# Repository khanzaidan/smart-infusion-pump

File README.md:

# 🏥 Smart Infusion Pump
### STM32F407 + FreeRTOS | Medical Grade | IEC 62304 Aligned

> Developed during Embedded R&D Internship at **Walnut Medical, Mohali**

---

## 📋 Project Overview
A safety-critical smart infusion pump featuring closed-loop PID flow 
control, real-time RTOS scheduling, Peltier temperature regulation, 
and WiFi monitoring — built on STM32F407VGT6 with FreeRTOS.

---

## 🔧 Hardware Architecture

| Component | Part | Function |
|-----------|------|----------|
| Main MCU | STM32F407VGT6 | FreeRTOS controller |
| Safety MCU | ATmega328P | Independent watchdog |
| WiFi | ESP32-WROOM-32UE | Remote monitoring |
| Motor Driver | DRV8825 | NEMA17 stepper |
| Pressure | MPRLS0015PG | Flow sensing |
| Temperature | DS18B20 x2 | Peltier control |
| Bubble Detect | BSTH-003 | Safety detection |
| Battery | BQ24650 + MAX17043 | Power management |
| Display | SSD1306 OLED | User interface |

---

## 🧵 FreeRTOS Task Structure

| Task | Priority | Stack |
|------|----------|-------|
| vMotorControlTask | AboveNormal | 512 |
| vSafetyMonitorTask | Realtime | 256 |
| vTemperatureTask | Normal | 256 |
| vDisplayTask | BelowNormal | 512 |
| vCommunicationTask | BelowNormal | 512 |
| vPressureTask | Normal | 256 |

---

## 📌 STM32F407 Pin Assignments

| Signal | Pin | Function |
|--------|-----|----------|
| USART1_TX/RX | PA9/PA10 | ESP32 WiFi |
| USART3_TX/RX | PD8/PD9 | ATmega Safety |
| I2C1_SCL/SDA | PB6/PB7 | OLED + EEPROM |
| I2C2_SCL/SDA | PB10/PB11 | Pressure + Fuel |
| TIM2_CH1 | PA0 | Peltier PWM |
| STEP_PUL/DIR/EN | PD11/PD12/PD13 | DRV8825 |
| TEMP_OW | PC9 | DS18B20 |
| RELAY_CTRL | PB15 | Motor Relay |
| BUZZ_SIG | PE1 | Buzzer |
| FAN_CTRL | PC8 | Cooling Fan |

---

## ⚙️ Clock Configuration
- HSE Crystal: 8MHz
- PLL: M=8, N=336, P=2
- SYSCLK: **168MHz**
- APB1: 42MHz | APB2: 84MHz

---

## 📐 PCB Specifications
- **Board Size:** 120mm x 100mm
- **Layers:** 2-layer with GND pour
- **Components:** 186
- **DRC Violations:** 0
- **Status:** Gerbers submitted to manufacturer

---

## 🛡️ Safety Features
- ATmega328P independent safety watchdog
- TPS3823 hardware watchdog timer
- Overcurrent protection
- Bubble detection alarm
- Limit switch monitoring
- Fault detection FSM
- EEPROM non-volatile parameter storage

---

[Browse the firmware by processor](docs/firmware-map.md)

## 📁 Repository Structure

```
smart-infusion-pump/
├── Core/                       STM32 application, headers and startup
├── Drivers/                    CMSIS and STM32 HAL
├── Middlewares/                FreeRTOS and middleware
├── SMART_INFUSION.ioc          STM32CubeMX configuration
├── SMART_INFUSION_ATmega/      ATmega companion sketch
├── SMART_INFUSION_ESP32/       ESP32 companion sketch
└── docs/firmware-map.md        Source index by processor
```

---

## 👤 Author
**Zaidan Khan** — Embedded R&D Intern @ Walnut Medical  
📧 khanzaidaan786@gmail.com  
🔗 [LinkedIn](https://linkedin.com/in/zaidan-khan-ab30922aa)

## Reference hardware files

[Telemetry observation fixture](hardware/README.md) is a newly drawn bench interface for this project. The hardware guide includes the pinout, KiCad and Altium projects, schematic PDF, routed PCB image, BOM, fabrication artwork and validation reports.

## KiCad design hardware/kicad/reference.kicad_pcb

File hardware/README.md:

# Telemetry observation fixture

Revision A · Reference hardware for Smart Infusion Pump

A passive two-channel observation card for replaying STM32 telemetry on the bench. One channel corresponds to USART1_TX (PA9) and the other to USART3_TX (PD8) in the checked-in CubeMX file.

This circuit was drawn for the portfolio from the interface description. Its connector numbering, board outline and part placements belong to this revision. Original product CAD, connector pinouts and measured results were unavailable. Physical bring-up is pending.

The top view overlays front copper in red, back copper in blue and silkscreen in brown. The board measures 63.50 × 45.72 mm. It uses two copper layers, plated through-hole components and 0.30 mm traces.

## Design files

| File | Use |
| --- | --- |
| [KiCad project](kicad/reference.kicad_pro) | Open in KiCad 9 with the included symbol table and symbol library. |
| [Altium project](altium/reference.PrjPcb) | Open the project with the adjacent native [schematic](altium/reference.SchDoc) and [PCB](altium/reference.PcbDoc). Components and land patterns are embedded in the placed documents. |
| [Schematic PDF](images/schematic.pdf) | Zoom or print the circuit, pin numbers and signal labels. |
| [PCB top view](images/copper.svg) | Inspect both routed copper layers and the assembly markings. |
| [Bill of materials](bom.csv) | Select parts to match the footprint and population notes. |
| [Gerber and drill ZIP](gerbers-and-drill.zip) | Review the manufacturing artwork for this reference revision. |

## Interface and wiring

Connect a development board or signal generator only. The card has no path back to an MCU RX pin, motor drive, fluid circuit or patient connection. Both analyzer channels are 3.3 V logic inputs.

Read the pin numbers from the component side. On each header the square pad marks pin 1. Use the table when wiring an external module.

| Header | Connector | Pin | Signal |
| --- | --- | ---: | --- |
| J1 | BENCH SRC | 1 | `GND` |
| J1 | BENCH SRC | 2 | `PA9_TX1` |
| J1 | BENCH SRC | 3 | `PD8_TX3` |
| J2 | ANALYZER | 1 | `GND` |
| J2 | ANALYZER | 2 | `MON_TX1` |
| J2 | ANALYZER | 3 | `MON_TX3` |

## Assembly and bench checks

Fit the headers and components according to the BOM. Confirm LED polarity where fitted. Check the board for shorts before attaching external equipment.

1. Confirm each source-to-monitor path measures approximately 1 kilohm and both channels are isolated from each other.
2. Replay two independent UART streams from a bench generator. Capture each output separately and confirm that interrupting the analyzer has no effect on the generator.

## Firmware connection

The original STM32 pin configuration identifies PA9 and PD8 as transmit outputs. Use a development board or a synthetic UART source to test capture. [Pinned CubeMX configuration](https://github.com/khanzaidan/smart-infusion-pump/blob/533e038e8589ce8a454668a1a26a9ea66db71109/SMART_INFUSION.ioc)

## Validation

KiCad 9.0.2 reported zero electrical-rule violations, zero PCB design-rule violations, zero unconnected pads and zero schematic-to-board parity errors. The exported schematic netlist matched the specified 10 pin assignments on 5 named nets. [Electrical report](validation/erc.rpt) · [PCB report](validation/drc.rpt)

The Altium files were read back with AltiumSharp. Connectivity reconstructed from the schematic geometry matched the net on each PCB pad. KiCad independently imported the Altium PCB and verified component designators, pad net names, pad widths and drill sizes, trace and via counts, and board dimensions. Altium Designer desktop opening, compilation, manufacturing review and physical measurements are pending.

## Sources

Project background follows the supplied résumé. KiCad Community through-hole land patterns are distributed under CC BY-SA 4.0 with the KiCad design exception. The layout image is a CAD plot of this board. [KiCad library license](https://www.kicad.org/libraries/license/) · [AltiumSharp file writer](https://github.com/issus/AltiumSharp/tree/5caeff2fc0b15c9b63f226ba3f872c65f7f39486)

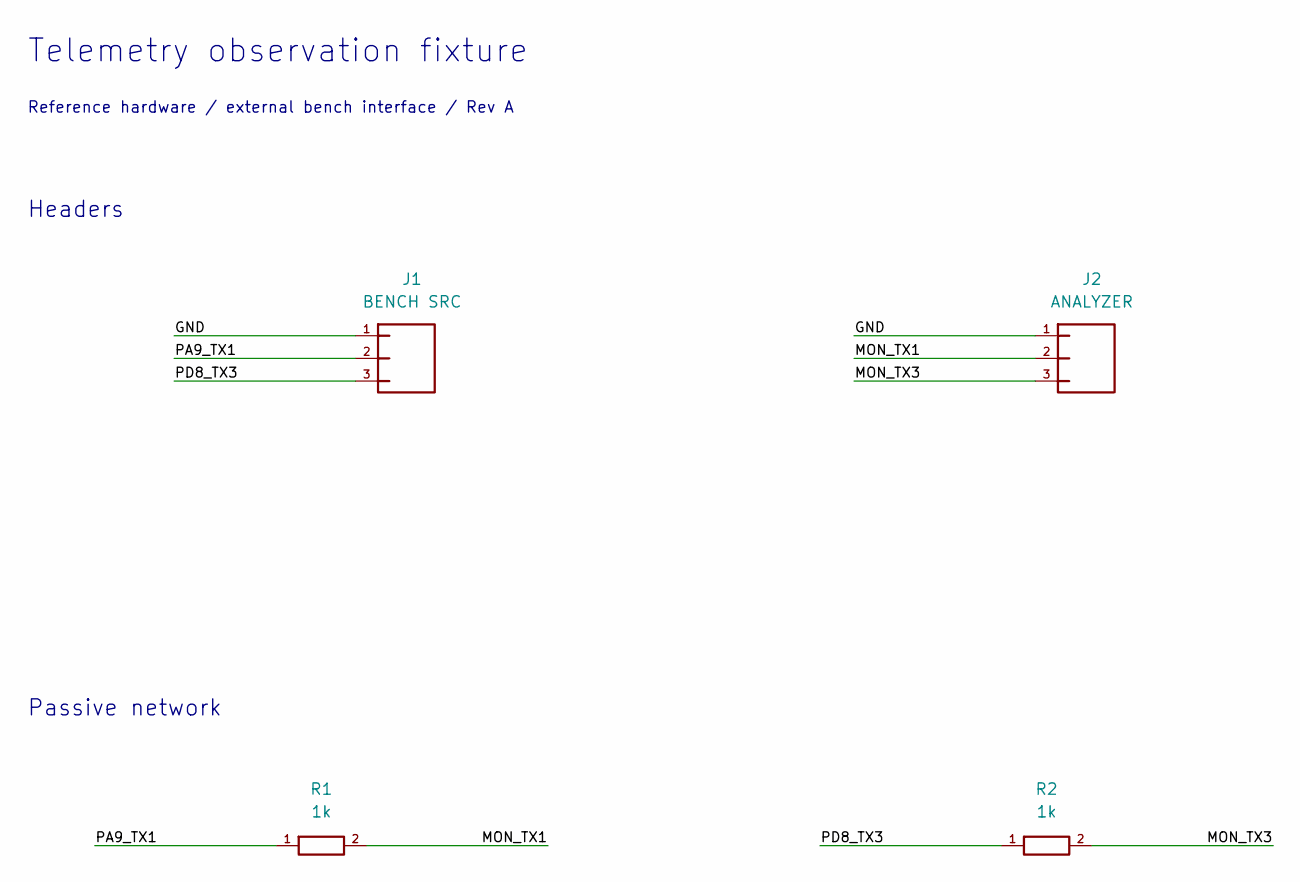
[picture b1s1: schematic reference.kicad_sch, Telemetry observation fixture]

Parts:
J1: BENCH SRC; PinHeader_1x03_P2.54mm_Vertical
J2: ANALYZER; PinHeader_1x03_P2.54mm_Vertical
R1, R2: 1k; R_Axial_DIN0207_L6.3mm_D2.5mm_P7.62mm_Horizontal

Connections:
/GND: J1.1, J2.1
/MON_TX1: J2.2, R1.2
/MON_TX3: J2.3, R2.2
/PA9_TX1: J1.2, R1.1
/PD8_TX3: J1.3, R2.1

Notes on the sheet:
Telemetry observation fixture
Reference hardware / external bench interface / Rev A
Headers
Passive network

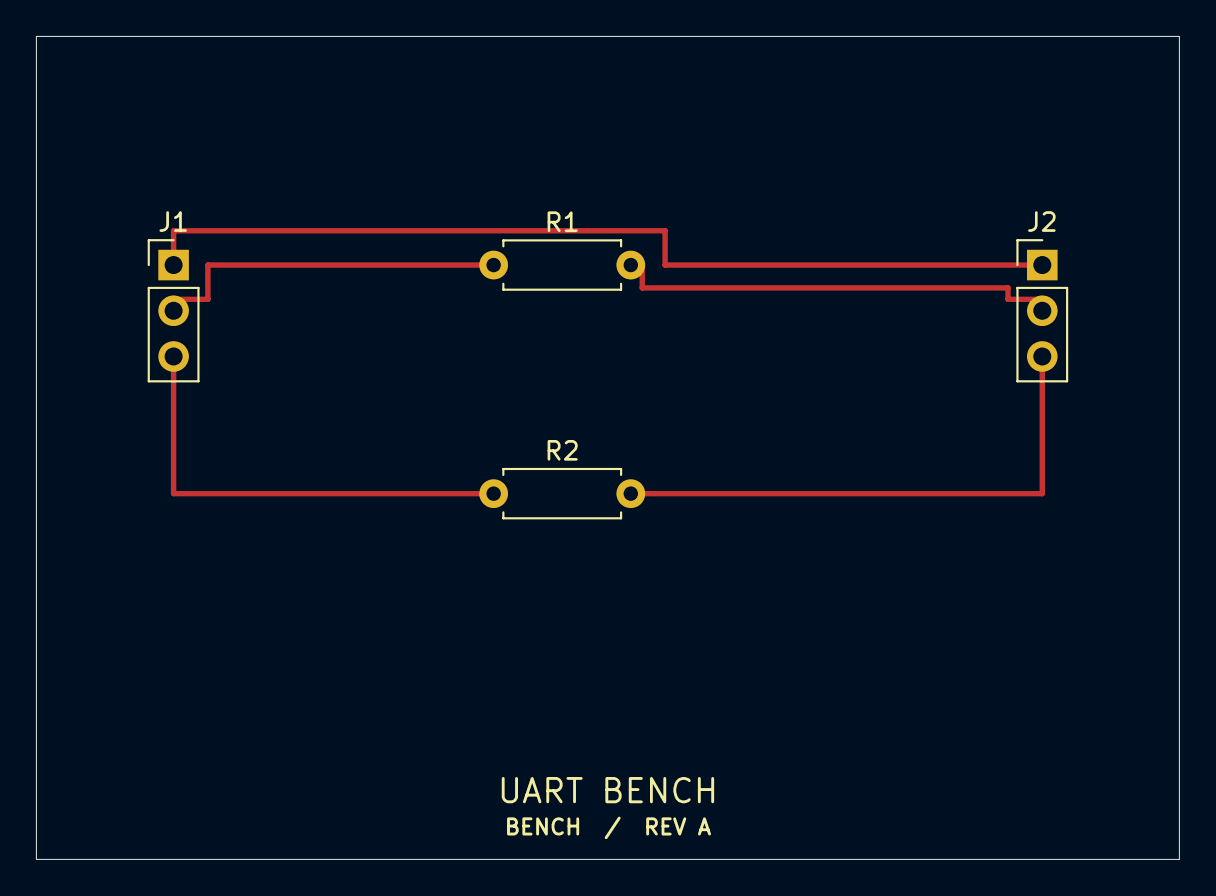
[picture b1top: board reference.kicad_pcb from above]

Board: 2 copper layers, 63.5 x 45.7 mm, 4 parts (0 on the bottom side), 5 nets.
